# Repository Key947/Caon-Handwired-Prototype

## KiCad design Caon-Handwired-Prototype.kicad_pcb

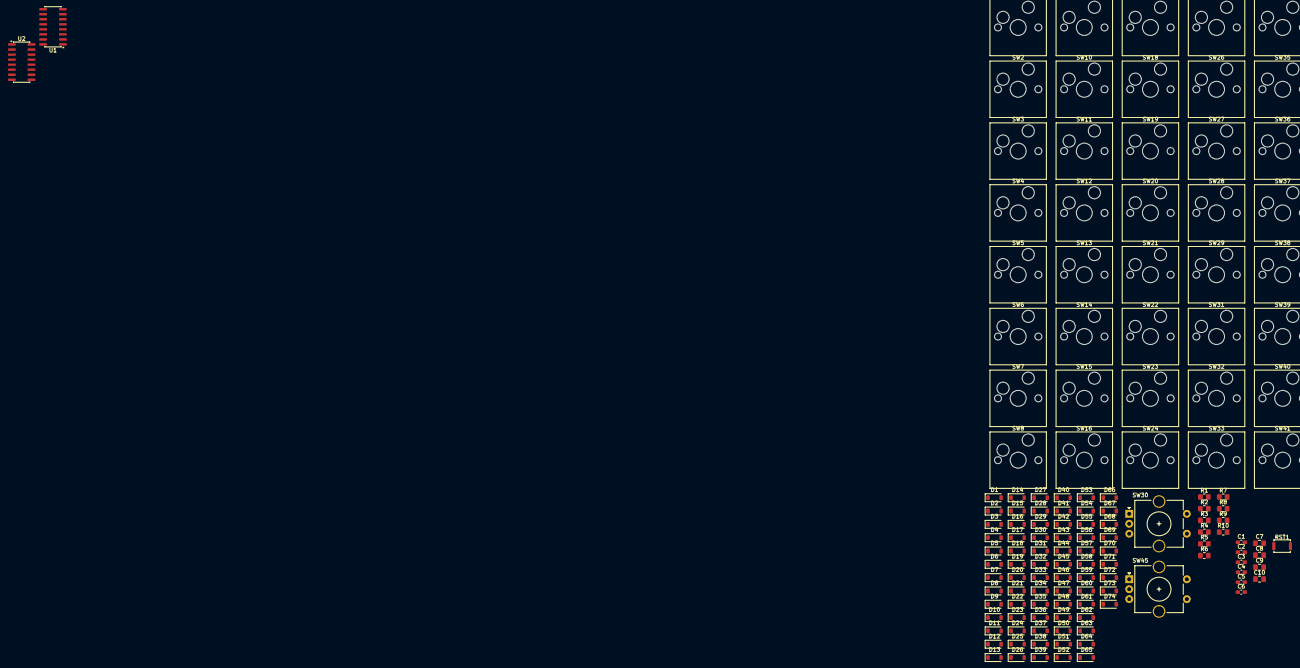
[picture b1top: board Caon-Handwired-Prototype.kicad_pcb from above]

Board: 4 copper layers, 171 parts (0 on the bottom side), 105 nets, no tracks yet.

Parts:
C1, C3, C5: 1uf; C_0603_1608Metric_Pad1.08x0.95mm_HandSolder
C2, C4, C6: 0.1uf; C_0603_1608Metric_Pad1.08x0.95mm_HandSolder
C7, C8, C9, C10: 10nf; C_0805_2012Metric_Pad1.18x1.45mm_HandSolder
D1, D2, D3, D4, D5, D6, D7, D8, D9, D10, D11, D12, D13, D14, D15, D16, D17, D18, D19, D20, D21, D22, D23, D24, D25, D26, D27, D28, D29, D30, D31, D32, D33, D34, D35, D36, D37, D38, D39, D40, D41, D42, D43, D44, D45, D46, D47, D48, D49, D50, D51, D52, D53, D54, D55, D56, D57, D58, D59, D60, D61, D62, D63, D64, D65, D66, D67, D68, D69, D70, D71, D72, D73, D74: 1N4148W; D_SOD-123
R1, R2, R3, R4, R5, R6, R7, R8, R9, R10: 10k; R_0805_2012Metric_Pad1.20x1.40mm_HandSolder
RST1: Switch; SW_Push_SPST_NO_Alps_SKRK
SW1, SW2, SW3, SW4, SW5, SW6, SW7, SW8, SW9, SW10, SW11, SW12, SW13, SW14, SW15, SW16, SW17, SW18, SW19, SW20, SW21, SW22, SW23, SW24, SW25, SW26, SW27, SW28, SW29, SW31, SW32, SW33, SW34, SW35, SW36, SW37, SW38, SW39, SW40, SW41, SW42, SW43, SW44, SW46, SW47, SW48, SW49, SW50, SW51, SW52, SW53, SW54, SW55, SW56, SW57, SW58, SW59, SW60, SW61, SW62, SW63, SW64, SW65, SW66, SW67, SW68, SW69, SW70, SW71, SW72, SW73, SW74: SW_Hotswap_Kailh_MX_1.00u
SW30, SW45: EC11 ENCODER 1; RotaryEncoder_Alps_EC11E-Switch_Vertical_H20mm_CircularMoun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
U1, U2: 74HC595; SOIC-16_3.9x9.9mm_P1.27mm

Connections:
+3V3: C1.1, C2.1, C3.1, C4.1, C5.1, C6.1, R1.2, R2.2, R3.1, R4.1, R7.1, R8.1, U1.10 (~SRCLR), U1.16 (VCC), U2.10 (~SRCLR), U2.16 (VCC)
C0: SW1.1, SW16.1, SW31.1, SW46.1, SW60.1, U1.1 (QB)
C1: SW2.1, SW17.1, SW32.1, SW47.1, SW61.1, U2.6 (QG)
C2: SW3.1, SW18.1, SW33.1, SW48.1, SW62.1, U1.2 (QC)
C3: SW4.1, SW19.1, SW34.1, SW49.1, SW63.1, U2.5 (QF)
C4: SW5.1, SW20.1, SW35.1, SW50.1, SW64.1, U1.3 (QD)
C5: SW6.1, SW21.1, SW36.1, SW51.1, SW65.1, U2.4 (QE)
C6: SW7.1, SW22.1, SW37.1, SW52.1, SW66.1, U1.4 (QE)
C7: SW8.1, SW23.1, SW38.1, SW53.1, SW67.1, U2.3 (QD)
C8: SW9.1, SW24.1, SW39.1, SW54.1, SW68.1, U1.5 (QF)
C9: SW10.1, SW25.1, SW40.1, SW55.1, SW69.1, U2.2 (QC)
C10: SW11.1, SW26.1, SW41.1, SW56.1, SW70.1, U1.6 (QG)
C11: SW12.1, SW27.1, SW42.1, SW57.1, SW71.1, U2.1 (QB)
C12: SW13.1, SW28.1, SW43.1, SW58.1, SW72.1, U1.7 (QH)
C13: SW14.1, SW29.1, SW44.1, SW59.1, SW73.1, U2.15 (QA)
C14: SW15.1, SW30.S2, SW45.S2, SW74.1, U1.15 (QA)
CS: U1.12 (RCLK), U2.12 (RCLK)
ENC1_A: C8.1, C10.1, R6.2, R10.2
ENC1_B: C7.1, C9.1, R5.2, R9.2
GND: C1.2, C2.2, C3.2, C4.2, C5.2, C6.2, C7.2, C8.2, C9.2, C10.2, RST1.2, SW30.C, SW45.C, U1.8 (GND), U1.13 (~OE), U2.8 (GND), U2.13 (~OE)
unnamed: D1.2 (A), SW1.2
unnamed: D2.2 (A), SW2.2
unnamed: D3.2 (A), SW3.2
unnamed: D4.2 (A), SW4.2
unnamed: D5.2 (A), SW5.2
unnamed: D6.2 (A), SW6.2
unnamed: D7.2 (A), SW7.2
unnamed: D8.2 (A), SW8.2
unnamed: D9.2 (A), SW9.2
unnamed: D10.2 (A), SW10.2
unnamed: D11.2 (A), SW11.2
unnamed: D12.2 (A), SW12.2
unnamed: D13.2 (A), SW13.2
unnamed: D14.2 (A), SW14.2
unnamed: D15.2 (A), SW15.2
unnamed: D16.2 (A), SW16.2
unnamed: D17.2 (A), SW17.2
unnamed: D18.2 (A), SW18.2
unnamed: D19.2 (A), SW19.2
unnamed: D20.2 (A), SW20.2
unnamed: D21.2 (A), SW21.2
unnamed: D22.2 (A), SW22.2
unnamed: D23.2 (A), SW23.2
unnamed: D24.2 (A), SW24.2
unnamed: D25.2 (A), SW25.2
unnamed: D26.2 (A), SW26.2
unnamed: D27.2 (A), SW27.2
unnamed: D28.2 (A), SW28.2
unnamed: D29.2 (A), SW29.2
unnamed: D30.2 (A), SW30.S1
unnamed: D31.2 (A), SW31.2
unnamed: D32.2 (A), SW32.2
unnamed: D33.2 (A), SW33.2
unnamed: D34.2 (A), SW34.2
unnamed: D35.2 (A), SW35.2
unnamed: D36.2 (A), SW36.2
unnamed: D37.2 (A), SW37.2
unnamed: D38.2 (A), SW38.2
unnamed: D39.2 (A), SW39.2
unnamed: D40.2 (A), SW40.2
unnamed: D41.2 (A), SW41.2
unnamed: D42.2 (A), SW42.2
unnamed: D43.2 (A), SW43.2
unnamed: D44.2 (A), SW44.2
unnamed: D45.2 (A), SW45.S1
unnamed: D46.2 (A), SW46.2
unnamed: D47.2 (A), SW47.2
unnamed: D48.2 (A), SW48.2
unnamed: D49.2 (A), SW49.2
unnamed: D50.2 (A), SW50.2
unnamed: D51.2 (A), SW51.2
unnamed: D52.2 (A), SW52.2
unnamed: D53.2 (A), SW53.2
unnamed: D54.2 (A), SW54.2
unnamed: D55.2 (A), SW55.2
unnamed: D56.2 (A), SW56.2
unnamed: D57.2 (A), SW57.2
unnamed: D58.2 (A), SW58.2
unnamed: D59.2 (A), SW59.2
unnamed: D60.2 (A), SW60.2
unnamed: D61.2 (A), SW61.2
unnamed: D62.2 (A), SW62.2
unnamed: D63.2 (A), SW63.2
unnamed: D64.2 (A), SW64.2
unnamed: D65.2 (A), SW65.2
unnamed: D66.2 (A), SW66.2
unnamed: D67.2 (A), SW67.2
unnamed: D68.2 (A), SW68.2
unnamed: D69.2 (A), SW69.2
unnamed: D70.2 (A), SW70.2
unnamed: D71.2 (A), SW71.2
unnamed: D72.2 (A), SW72.2
unnamed: D73.2 (A), SW73.2
unnamed: D74.2 (A), SW74.2
unnamed: R3.2, R5.1, SW30.B
unnamed: R4.2, R6.1, SW30.A
unnamed: R7.2, R9.1, SW45.B
unnamed: R8.2, R10.1, SW45.A
QH': U1.9 (QH'), U2.14 (SER)
R0: D1.1 (K), D2.1 (K), D3.1 (K), D4.1 (K), D5.1 (K), D6.1 (K), D7.1 (K), D8.1 (K), D9.1 (K), D10.1 (K), D11.1 (K), D12.1 (K), D13.1 (K), D14.1 (K), D15.1 (K)
R1: D16.1 (K), D17.1 (K), D18.1 (K), D19.1 (K), D20.1 (K), D21.1 (K), D22.1 (K), D23.1 (K), D24.1 (K), D25.1 (K), D26.1 (K), D27.1 (K), D28.1 (K), D29.1 (K), D30.1 (K)
R2: D31.1 (K), D32.1 (K), D33.1 (K), D34.1 (K), D35.1 (K), D36.1 (K), D37.1 (K), D38.1 (K), D39.1 (K), D40.1 (K), D41.1 (K), D42.1 (K), D43.1 (K), D44.1 (K), D45.1 (K)
R3: D46.1 (K), D47.1 (K), D48.1 (K), D49.1 (K), D50.1 (K), D51.1 (K), D52.1 (K), D53.1 (K), D54.1 (K), D55.1 (K), D56.1 (K), D57.1 (K), D58.1 (K), D59.1 (K)
R4: D60.1 (K), D61.1 (K), D62.1 (K), D63.1 (K), D64.1 (K), D65.1 (K), D66.1 (K), D67.1 (K), D68.1 (K), D69.1 (K), D70.1 (K), D71.1 (K), D72.1 (K), D73.1 (K), D74.1 (K)
SCK: U1.11 (SRCLK), U2.11 (SRCLK)

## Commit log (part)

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2025-10-04 Innitial commit
2025-10-04 Schemmatic Update
2025-10-04 Schematic Update
2025-10-05 Schematic and Footprint Update
2025-10-05 Schematic, Footprint, PCB Update
2025-10-10 bump version to V0.1
2025-10-10 v0.11
2025-10-11 v0.2
2025-10-11 fix: 2nd 595 as 2nd Device
    instead of daisy chained
2025-10-12 Added pin description for firmware development
2025-10-15 Schematic and PCB Update
2026-03-14 Oled protection circuits
2026-03-14 Updated OLED protection circuit
2026-03-15 Readibility
2026-04-05 Oled Protection ciruit
2026-04-05 decaps on shifter
